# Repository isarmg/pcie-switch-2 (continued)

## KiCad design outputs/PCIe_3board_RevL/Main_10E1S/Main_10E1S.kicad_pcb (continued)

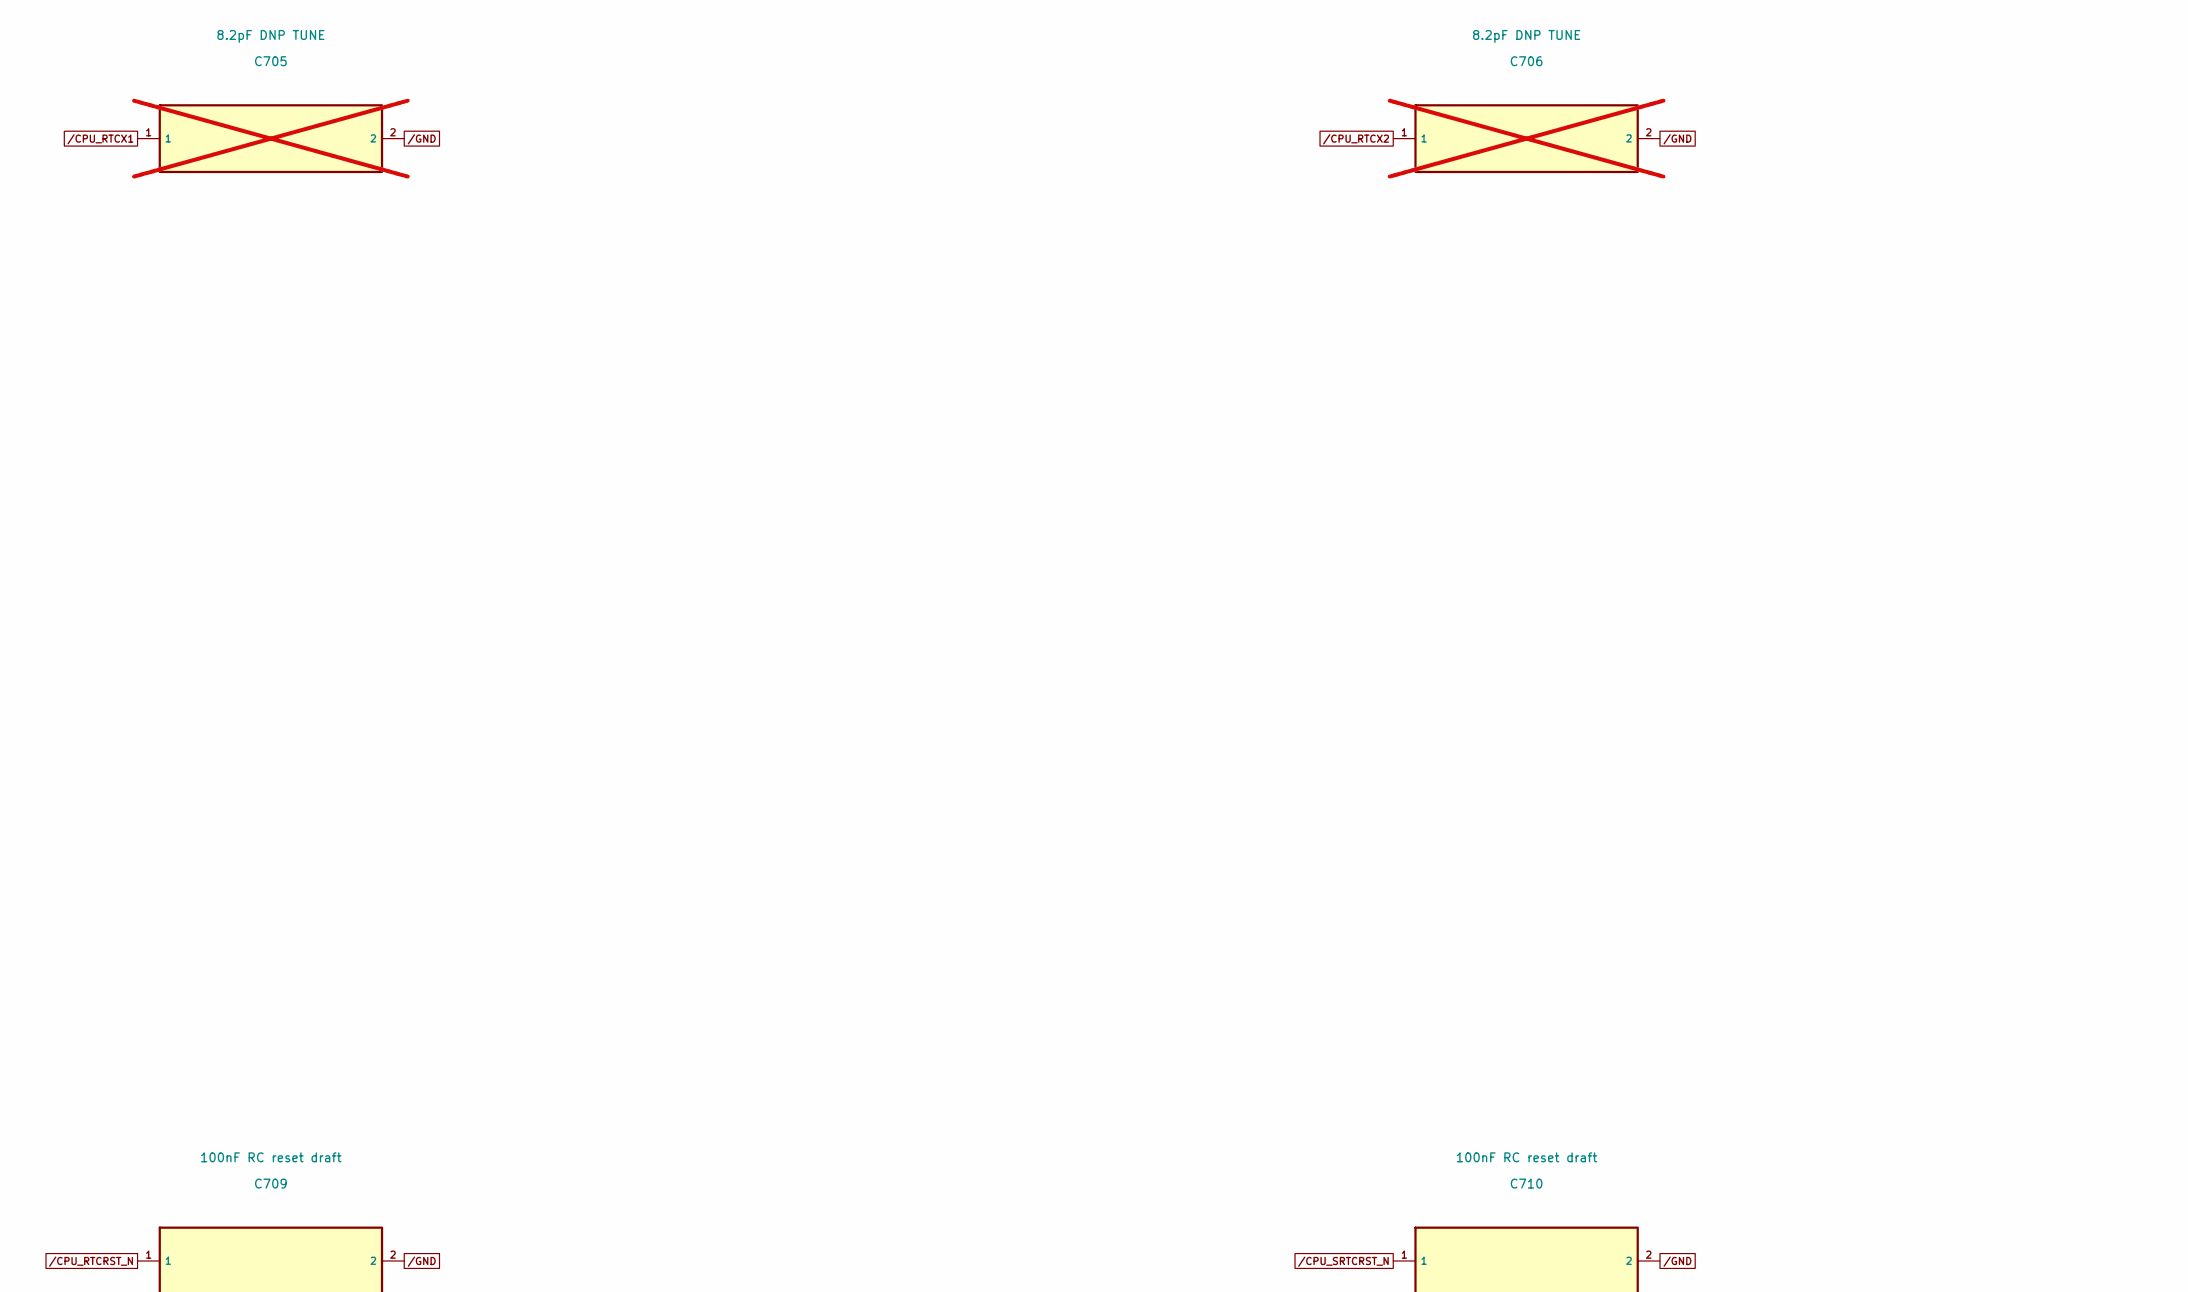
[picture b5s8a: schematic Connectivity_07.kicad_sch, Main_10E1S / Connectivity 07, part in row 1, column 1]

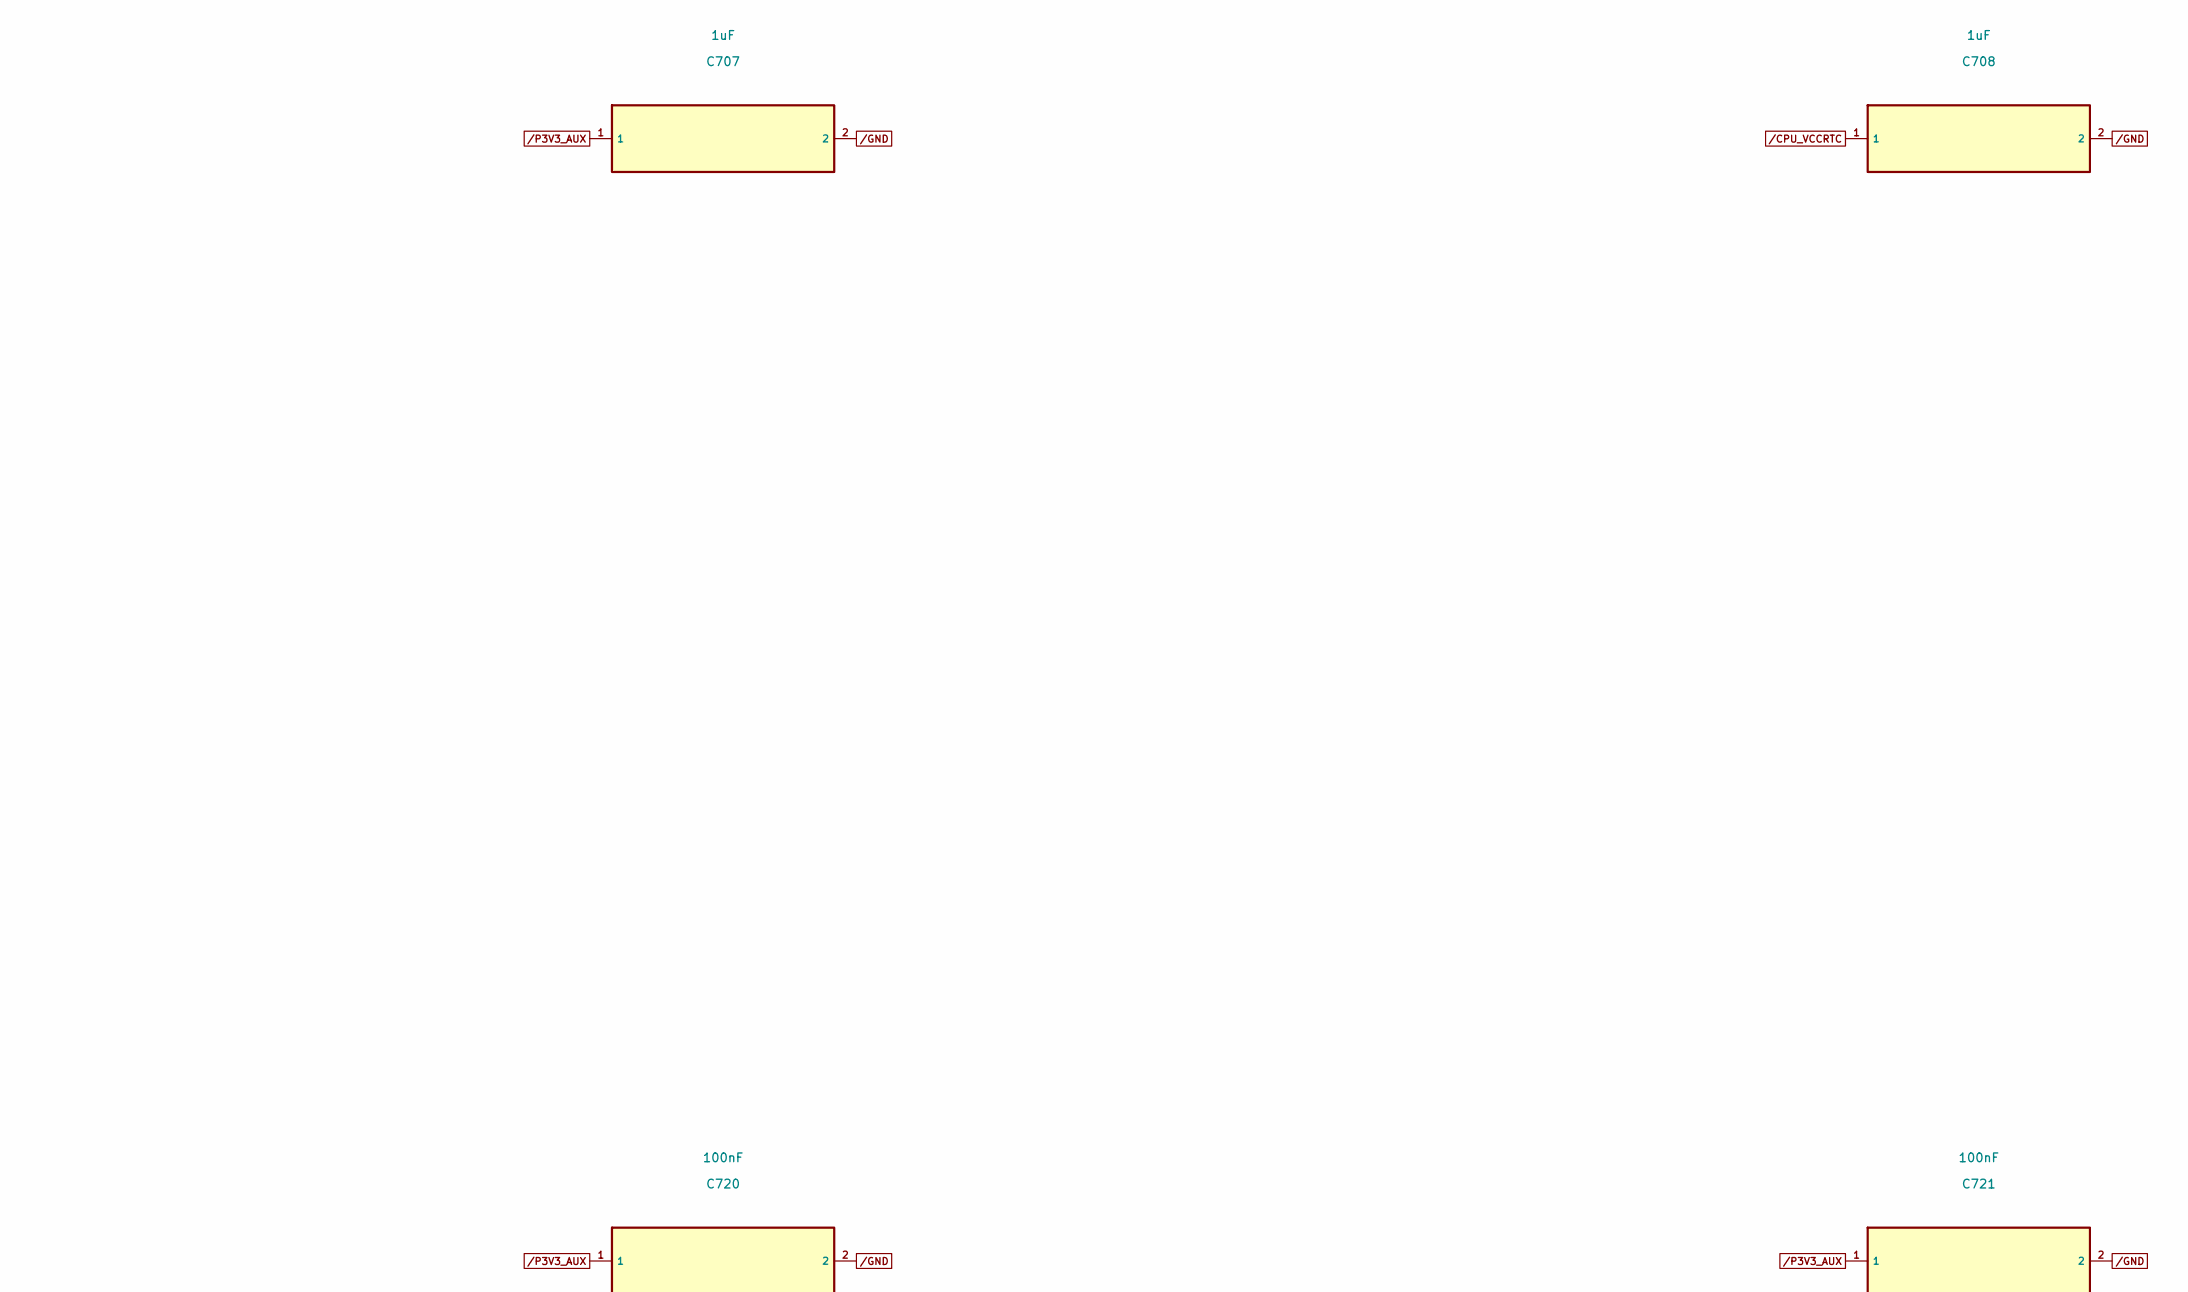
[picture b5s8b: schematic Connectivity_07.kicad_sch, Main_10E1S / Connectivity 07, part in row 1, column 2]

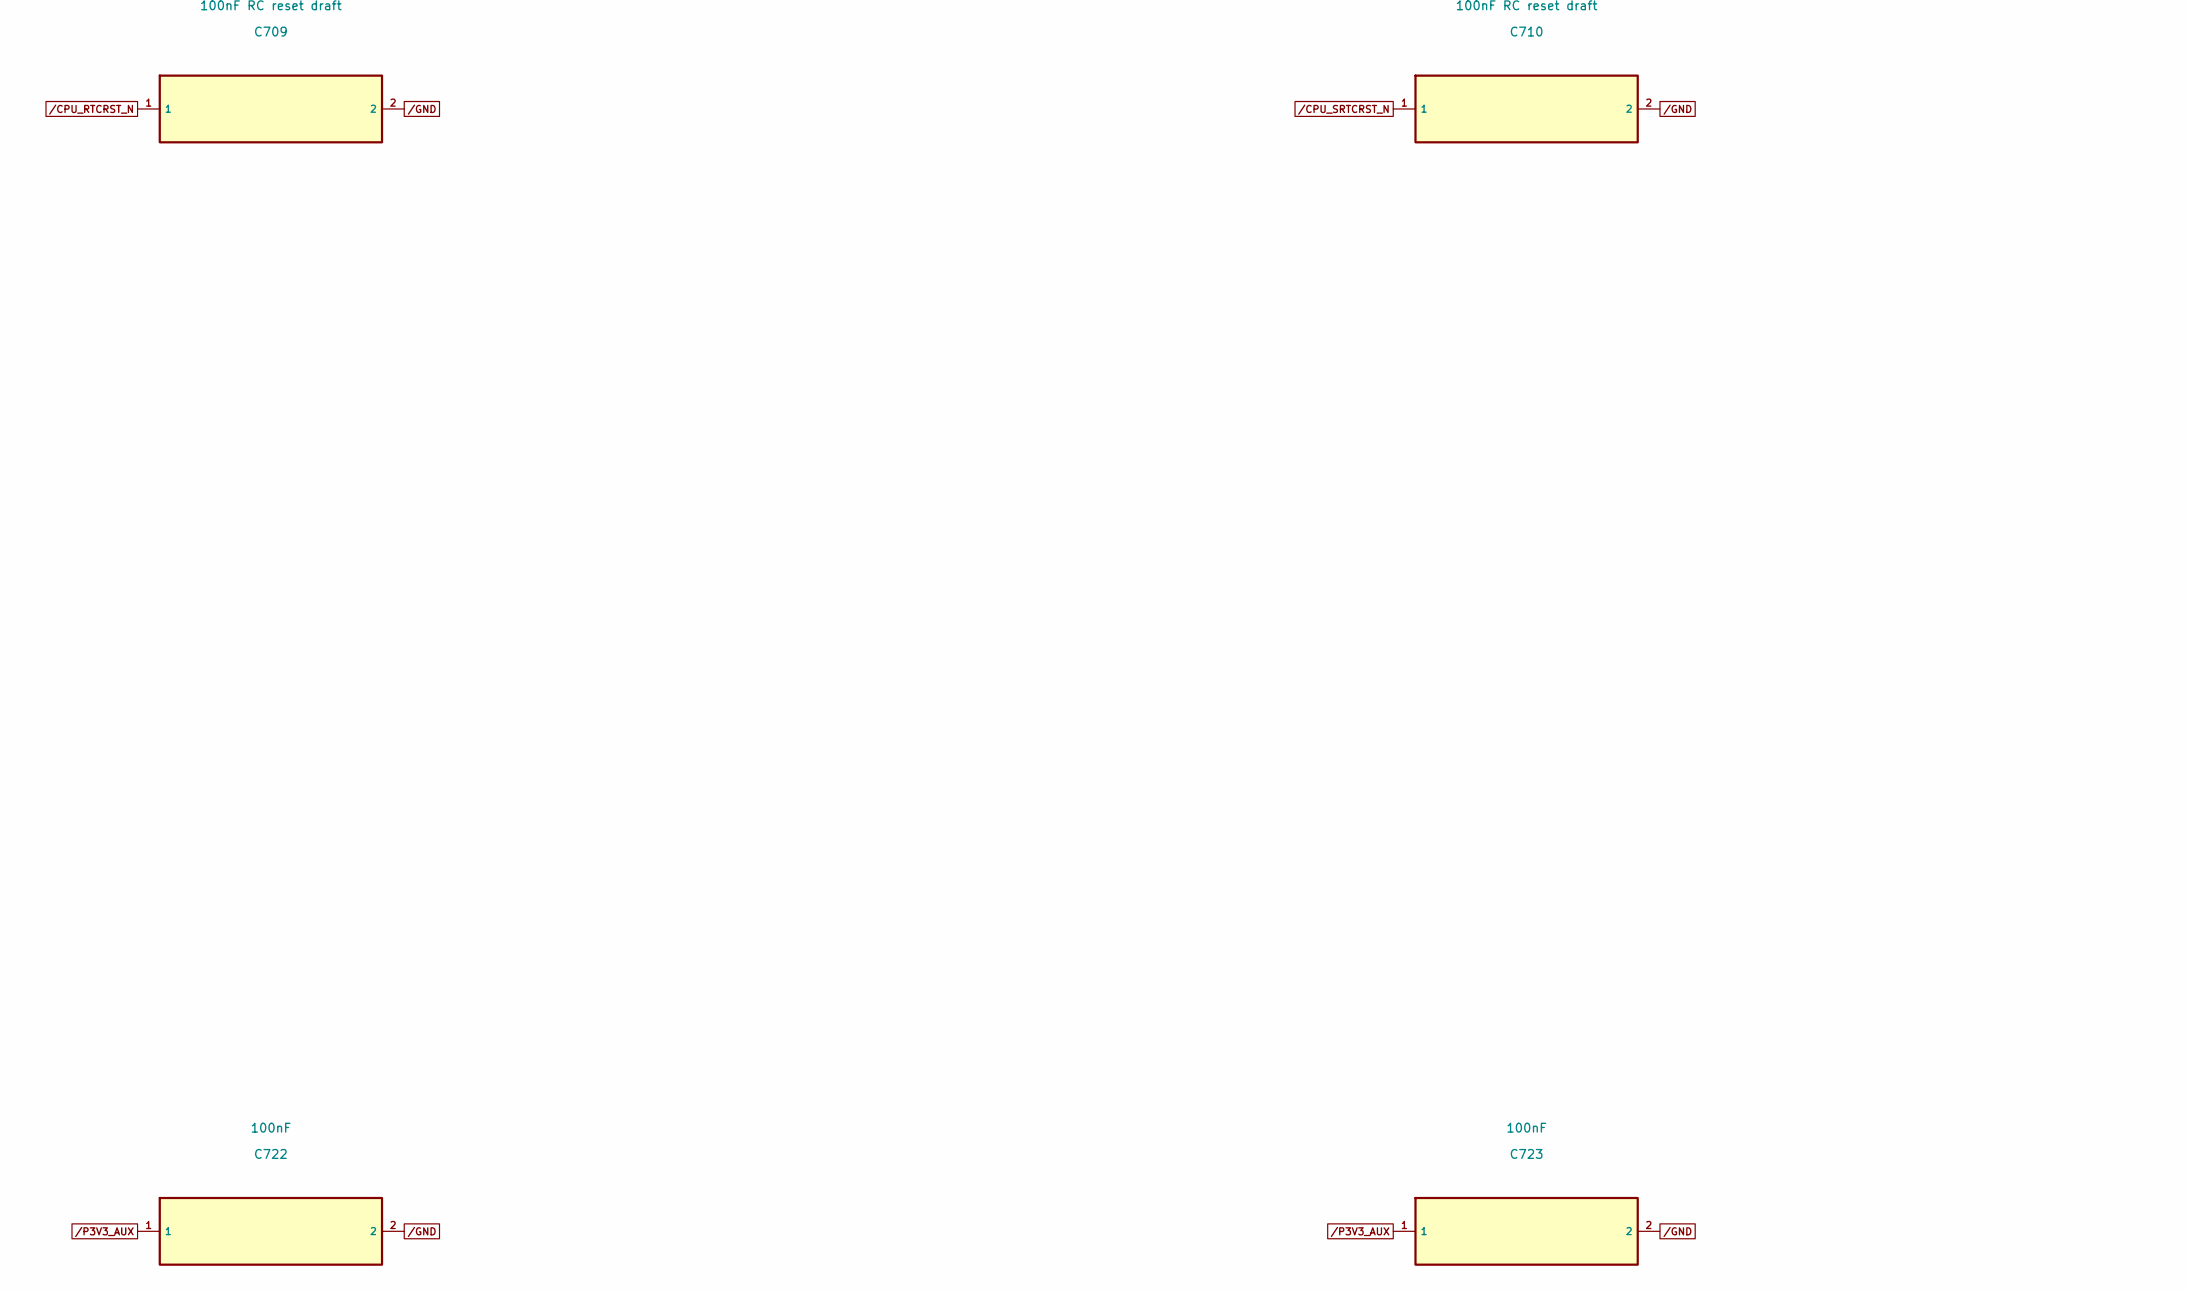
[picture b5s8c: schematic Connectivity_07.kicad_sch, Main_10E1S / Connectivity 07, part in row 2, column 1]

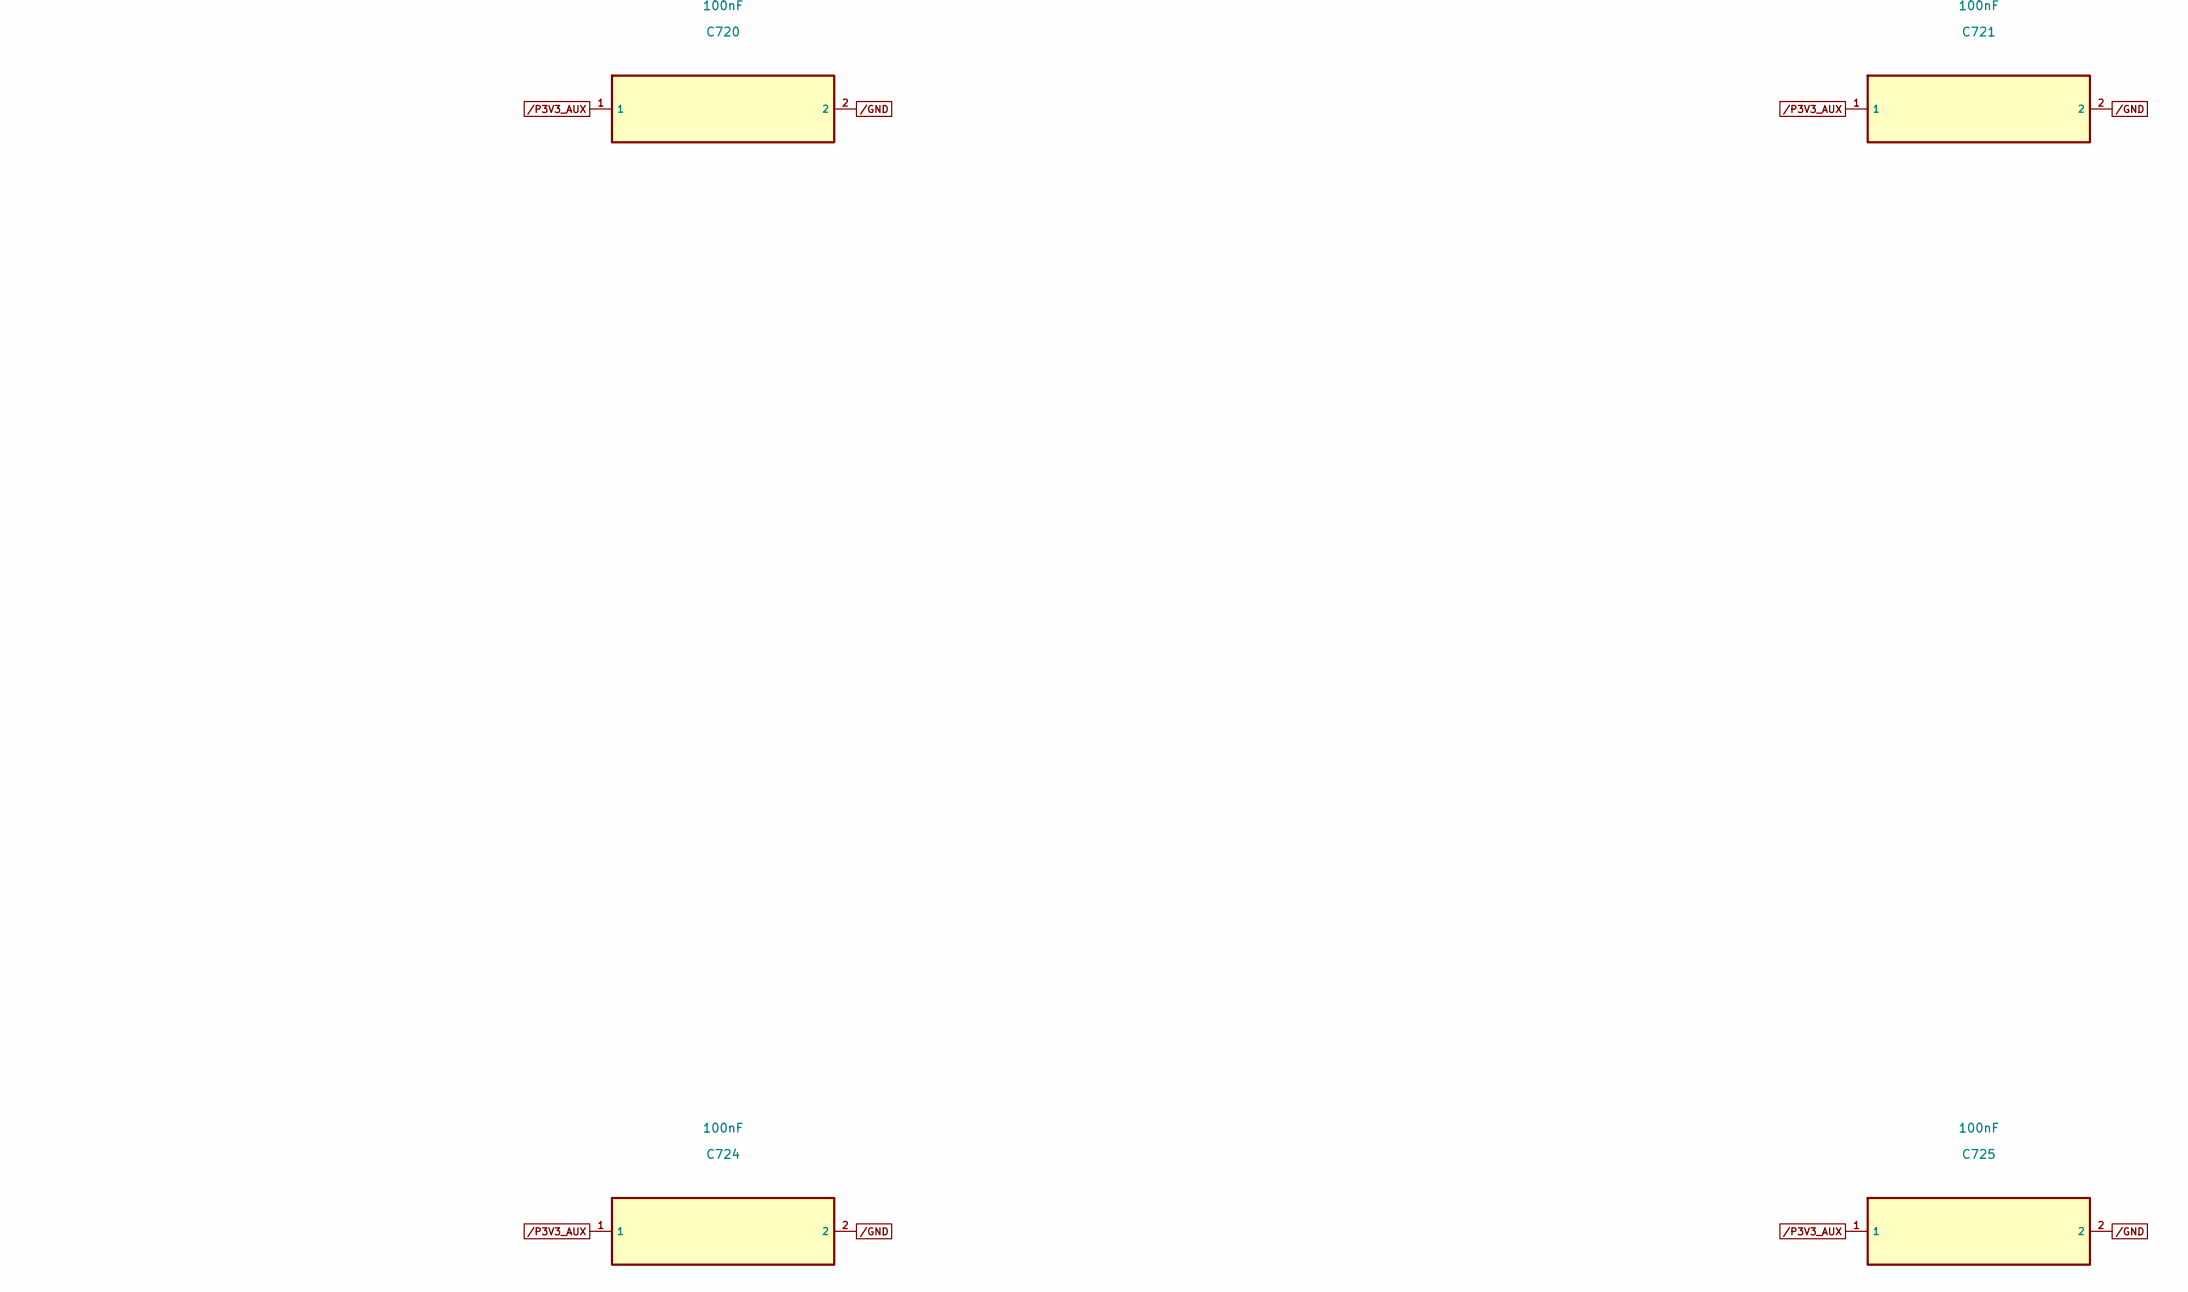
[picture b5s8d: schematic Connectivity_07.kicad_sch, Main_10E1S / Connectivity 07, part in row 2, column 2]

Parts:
C705, C706: 8.2pF DNP TUNE; C_0402_1005Metric; not fitted
C707, C708: 1uF; C_0402_1005Metric
C709, C710: 100nF RC reset draft; C_0402_1005Metric
C720, C721, C722, C723, C724, C725: 100nF; C_0402_1005Metric

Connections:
/CPU_RTCRST_N: C709.1; also elsewhere on the board
/CPU_RTCX1: C705.1; also elsewhere on the board
/CPU_RTCX2: C706.1; also elsewhere on the board
/CPU_SRTCRST_N: C710.1; also elsewhere on the board
/CPU_VCCRTC: C708.1; also elsewhere on the board
/GND: C705.2, C706.2, C707.2, C708.2, C709.2, C710.2, C720.2, C721.2, C722.2, C723.2, C724.2, C725.2; also elsewhere on the board
/P3V3_AUX: C707.1, C720.1, C721.1, C722.1, C723.1, C724.1, C725.1; also elsewhere on the board

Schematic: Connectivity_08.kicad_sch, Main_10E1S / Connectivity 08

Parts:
C726, C727, C728, C730, C731, C732, C733, C734, C735, C736, C737, C738: 100nF; C_0402_1005Metric

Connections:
/CLKBUF1_VDDA: C728.1; also elsewhere on the board
/CLKBUF2_VDDA: C738.1; also elsewhere on the board
/GND: C726.2, C727.2, C728.2, C730.2, C731.2, C732.2, C733.2, C734.2, C735.2, C736.2, C737.2, C738.2; also elsewhere on the board
/P3V3_AUX: C726.1, C727.1, C730.1, C731.1, C732.1, C733.1, C734.1, C735.1, C736.1, C737.1; also elsewhere on the board

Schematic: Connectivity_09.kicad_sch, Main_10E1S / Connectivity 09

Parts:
C741: 47nF / reset delay; C_0402_1005Metric
C742: 100nF; C_0402_1005Metric
C801, C802, C803, C804, C805, C806, C807, C808, C811, C812: 220nF 6.3V X5R; C_0402_1005Metric

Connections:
/CPU_G5_RX0_N: C812.2; also elsewhere on the board
/CPU_G5_RX0_P: C811.2; also elsewhere on the board
/CPU_G5_TX0_N: C802.1; also elsewhere on the board
/CPU_G5_TX0_P: C801.1; also elsewhere on the board
/CPU_G5_TX1_N: C804.1; also elsewhere on the board
/CPU_G5_TX1_P: C803.1; also elsewhere on the board
/CPU_G5_TX2_N: C806.1; also elsewhere on the board
/CPU_G5_TX2_P: C805.1; also elsewhere on the board
/CPU_G5_TX3_N: C808.1; also elsewhere on the board
/CPU_G5_TX3_P: C807.1; also elsewhere on the board
/CPU_PEX_RX0_N: C802.2; also elsewhere on the board
/CPU_PEX_RX0_P: C801.2; also elsewhere on the board
/CPU_PEX_RX1_N: C804.2; also elsewhere on the board
/CPU_PEX_RX1_P: C803.2; also elsewhere on the board
/CPU_PEX_RX2_N: C806.2; also elsewhere on the board
/CPU_PEX_RX2_P: C805.2; also elsewhere on the board
/CPU_PEX_RX3_N: C808.2; also elsewhere on the board
/CPU_PEX_RX3_P: C807.2; also elsewhere on the board
/CPU_PEX_TX0_N: C812.1; also elsewhere on the board
/CPU_PEX_TX0_P: C811.1; also elsewhere on the board
/GND: C741.2, C742.2; also elsewhere on the board
/P3V3_AUX: C742.1; also elsewhere on the board
/PEX_RESET_CT: C741.1; also elsewhere on the board

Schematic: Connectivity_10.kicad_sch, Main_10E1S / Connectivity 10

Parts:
C813, C814, C815, C816, C817, C818: 220nF 6.3V X5R; C_0402_1005Metric
C901, C903, C905: 100nF / PDN budget; C_0402_1005Metric
C902, C904, C906: 4.7uF / PDN budget; C_0603_1608Metric

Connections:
/CPU_G5_RX1_N: C814.2; also elsewhere on the board
/CPU_G5_RX1_P: C813.2; also elsewhere on the board
/CPU_G5_RX2_N: C816.2; also elsewhere on the board
/CPU_G5_RX2_P: C815.2; also elsewhere on the board
/CPU_G5_RX3_N: C818.2; also elsewhere on the board
/CPU_G5_RX3_P: C817.2; also elsewhere on the board
/CPU_PEX_TX1_N: C814.1; also elsewhere on the board
/CPU_PEX_TX1_P: C813.1; also elsewhere on the board
/CPU_PEX_TX2_N: C816.1; also elsewhere on the board
/CPU_PEX_TX2_P: C815.1; also elsewhere on the board
/CPU_PEX_TX3_N: C818.1; also elsewhere on the board
/CPU_PEX_TX3_P: C817.1; also elsewhere on the board
/CPU_V1P8U_MEM: C901.1, C902.1; also elsewhere on the board
/CPU_VCCGT: C903.1, C904.1; also elsewhere on the board
/CPU_VCCL2: C905.1, C906.1; also elsewhere on the board
/GND: C901.2, C902.2, C903.2, C904.2, C905.2, C906.2; also elsewhere on the board

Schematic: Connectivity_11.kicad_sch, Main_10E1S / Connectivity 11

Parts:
C907, C909, C911, C913, C915, C917: 100nF / PDN budget; C_0402_1005Metric
C908, C910, C912, C914, C916, C918: 4.7uF / PDN budget; C_0603_1608Metric

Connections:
/CPU_VCCPRIM_1P8: C907.1, C908.1; also elsewhere on the board
/CPU_VCCPRIM_3P3: C909.1, C910.1; also elsewhere on the board
/CPU_VCCPRIM_IO: C911.1, C912.1; also elsewhere on the board
/CPU_VCCPRIM_VNNAON: C913.1, C914.1; also elsewhere on the board
/CPU_VCCPRIM_VNNAONLV: C915.1, C916.1; also elsewhere on the board
/CPU_VCCRTC: C917.1, C918.1; also elsewhere on the board
/GND: C907.2, C908.2, C909.2, C910.2, C911.2, C912.2, C913.2, C914.2, C915.2, C916.2, C917.2, C918.2; also elsewhere on the board

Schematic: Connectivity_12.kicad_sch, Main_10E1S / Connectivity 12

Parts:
C919, C921, C923, C925, C927, C929: 100nF / PDN budget; C_0402_1005Metric
C920, C922, C924, C926, C928, C930: 4.7uF / PDN budget; C_0603_1608Metric

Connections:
/CPU_VCCSA: C919.1, C920.1; also elsewhere on the board
/CPU_VCCST: C921.1, C922.1; also elsewhere on the board
/CPU_VCC_ECORE: C923.1, C924.1; also elsewhere on the board
/CPU_VCC_PCORE: C925.1, C926.1; also elsewhere on the board
/CPU_VDD2H: C927.1, C928.1; also elsewhere on the board
/CPU_VDD2L: C929.1, C930.1; also elsewhere on the board
/GND: C919.2, C920.2, C921.2, C922.2, C923.2, C924.2, C925.2, C926.2, C927.2, C928.2, C929.2, C930.2; also elsewhere on the board

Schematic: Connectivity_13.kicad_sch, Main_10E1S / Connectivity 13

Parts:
C931, C933: 100nF / PDN budget; C_0402_1005Metric
C932, C934: 4.7uF / PDN budget; C_0603_1608Metric
C951, C952, C953, C954, C955, C956, C957, C958: 4.7uF / EDGECAP value pending PDG; C_0603_1608Metric

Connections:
/CPU_V1P8U_MEM_EDGECAP_0: C951.1; also elsewhere on the board
/CPU_V1P8U_MEM_EDGECAP_1: C952.1; also elsewhere on the board
/CPU_V1P8U_MEM_EDGECAP_2: C953.1; also elsewhere on the board
/CPU_V1P8U_MEM_EDGECAP_3: C954.1; also elsewhere on the board
/CPU_VDD2H_EDGECAP_0: C955.1; also elsewhere on the board
/CPU_VDD2H_EDGECAP_1: C956.1; also elsewhere on the board
/CPU_VDD2L_EDGECAP_0: C957.1; also elsewhere on the board
/CPU_VDD2L_EDGECAP_1: C958.1; also elsewhere on the board
/CPU_VDDQ: C931.1, C932.1; also elsewhere on the board
/CPU_VDDRIO: C933.1, C934.1; also elsewhere on the board
/GND: C931.2, C932.2, C933.2, C934.2, C951.2, C952.2, C953.2, C954.2, C955.2, C956.2, C957.2, C958.2; also elsewhere on the board

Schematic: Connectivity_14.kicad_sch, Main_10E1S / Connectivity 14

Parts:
C959, C960: 4.7uF / EDGECAP value pending PDG; C_0603_1608Metric
C965, C966, C967, C968: 1uF / filter value pending PDG; C_0402_1005Metric
D1, D2: SMBJ13CA; D_SMB
F1, F2: 20A 125V; Littelfuse_456_20A
J1, J2: HSEC6-028-01-S-DV-WT-TR; Samtec_HSEC6-028-01-S-DV-WT

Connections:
/CPU_VCCPRIM_1P8_FLTRA_IN: C966.1; also elsewhere on the board
/CPU_VCCPRIM_1P8_FLTRB_CAP: C965.1; also elsewhere on the board
/CPU_VCCPRIM_1P8_FLTRB_IN: C967.1; also elsewhere on the board
/CPU_VCCPRIM_VNNAON_FLTR: C968.1; also elsewhere on the board
/CPU_VDDQ_EDGECAP_0: C959.1; also elsewhere on the board
/CPU_VDDQ_EDGECAP_1: C960.1; also elsewhere on the board
/GND: C959.2, C960.2, C965.2, C966.2, C967.2, C968.2, D1.2, D2.2, J1.A1, J1.A2, J1.A3, J1.A4, J1.A5, J1.A6, J1.A13, J1.A16, J1.A19, J1.A22, J1.A25, J1.A28, J1.B13, J1.B16, J1.B19, J1.B22, J1.B25, J1.B28, J2.A1, J2.A2, J2.A3, J2.A4, J2.A5, J2.A6, J2.A13, J2.A16, J2.A19, J2.A22, J2.A25, J2.A28, J2.B13, J2.B16, J2.B19, J2.B22, J2.B25, J2.B28; also elsewhere on the board
/P3V3_AUX: J1.B11, J2.B11; also elsewhere on the board
/P12_SLOT01: J1.B1, J1.B2, J1.B3, J1.B4, J1.B5, J1.B6; also elsewhere on the board
/P12_SLOT02: J2.B1, J2.B2, J2.B3, J2.B4, J2.B5, J2.B6; also elsewhere on the board
/S01_DUALPORTEN_N: J1.B9
/S01_LED: J1.A10
/S01_PERST0_N: J1.B10
/S01_PERST1_CLKREQ_N: J1.A11
/S01_PRSNT0_N: J1.A12
/S01_PWRDIS: J1.B12
/S01_REFCLK0_N: J1.B14; also elsewhere on the board
/S01_REFCLK0_P: J1.B15; also elsewhere on the board
/S01_REFCLK1_N: J1.A14
/S01_REFCLK1_P: J1.A15
/S01_SMBCLK_I3CCLK: J1.A7
/S01_SMBDATA_I3CDATA: J1.A8
/S01_SMRST_N: J1.A9
/S01_SW_RX0_N: J1.A17; also elsewhere on the board
/S01_SW_RX0_P: J1.A18; also elsewhere on the board
/S01_SW_RX1_N: J1.A20; also elsewhere on the board
/S01_SW_RX1_P: J1.A21; also elsewhere on the board
/S01_SW_RX2_N: J1.A23; also elsewhere on the board
/S01_SW_RX2_P: J1.A24; also elsewhere on the board
/S01_SW_RX3_N: J1.A26; also elsewhere on the board
/S01_SW_RX3_P: J1.A27; also elsewhere on the board
/S01_SW_TX0_N: J1.B17; also elsewhere on the board
/S01_SW_TX0_P: J1.B18; also elsewhere on the board
/S01_SW_TX1_N: J1.B20; also elsewhere on the board
/S01_SW_TX1_P: J1.B21; also elsewhere on the board
/S01_SW_TX2_N: J1.B23; also elsewhere on the board
/S01_SW_TX2_P: J1.B24; also elsewhere on the board
/S01_SW_TX3_N: J1.B26; also elsewhere on the board
/S01_SW_TX3_P: J1.B27; also elsewhere on the board
/S02_DUALPORTEN_N: J2.B9
/S02_LED: J2.A10
/S02_PERST0_N: J2.B10
/S02_PERST1_CLKREQ_N: J2.A11
/S02_PRSNT0_N: J2.A12
/S02_PWRDIS: J2.B12
/S02_REFCLK0_N: J2.B14; also elsewhere on the board
/S02_REFCLK0_P: J2.B15; also elsewhere on the board
/S02_REFCLK1_N: J2.A14
/S02_REFCLK1_P: J2.A15
/S02_SMBCLK_I3CCLK: J2.A7
/S02_SMBDATA_I3CDATA: J2.A8
/S02_SMRST_N: J2.A9
/S02_SW_RX0_N: J2.A17; also elsewhere on the board
/S02_SW_RX0_P: J2.A18; also elsewhere on the board
/S02_SW_RX1_N: J2.A20; also elsewhere on the board
/S02_SW_RX1_P: J2.A21; also elsewhere on the board
/S02_SW_RX2_N: J2.A23; also elsewhere on the board
/S02_SW_RX2_P: J2.A24; also elsewhere on the board
/S02_SW_RX3_N: J2.A26; also elsewhere on the board
/S02_SW_RX3_P: J2.A27; also elsewhere on the board
/S02_SW_TX0_N: J2.B17; also elsewhere on the board
/S02_SW_TX0_P: J2.B18; also elsewhere on the board
/S02_SW_TX1_N: J2.B20; also elsewhere on the board
/S02_SW_TX1_P: J2.B21; also elsewhere on the board
/S02_SW_TX2_N: J2.B23; also elsewhere on the board
/S02_SW_TX2_P: J2.B24; also elsewhere on the board
/S02_SW_TX3_N: J2.B26; also elsewhere on the board
/S02_SW_TX3_P: J2.B27; also elsewhere on the board
/VBANK_A: D1.1, F1.2; also elsewhere on the board
/VBANK_B: D2.1, F2.2; also elsewhere on the board
/VIN_A: F1.1; also elsewhere on the board
/VIN_B: F2.1; also elsewhere on the board
